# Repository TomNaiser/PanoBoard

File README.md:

# PanoBoard
Integrated Electronics Board for a Gigapixel Panorama Head (pan and tilt motion)
-Arduino nano based controller
-bluetooth communication with the windowsbased control notebook
-PID position control (modified RC-Servos)
-rotatory position encoders for precise position control 

The latest version PanoBoardV5 is a size-reduced version. With the shrunken electronics box the panorama rig fits into my photo backpack. 

## Arduino Nano R4 upgrade

The [PanoBoard V5 Nano R4 patch](PanoBoard5KiCad/Nano-R4-Patch.md) explains the resistor changes, GPIO current limits, encoder I²C pull-ups, power supply and firmware porting needed to replace the classic Nano with a Nano R4. The KiCad files remain the original V5 design; apply the documented rework before operating the R4.

Current software: [PanoDuinoControl firmware](https://github.com/TomNaiser/PanoDuinoControl), [Android app and system documentation](https://github.com/TomNaiser/PanoramaSoftware), and [PanoramaControl for Windows](https://github.com/TomNaiser/PanoramaControl).

Warning! The circuits in this project were designed as a hobbyist project and may contain unintentional mistakes.  I don't take any responsibility for damages caused by using the above circuit design. Please use the provided information at your own risk!

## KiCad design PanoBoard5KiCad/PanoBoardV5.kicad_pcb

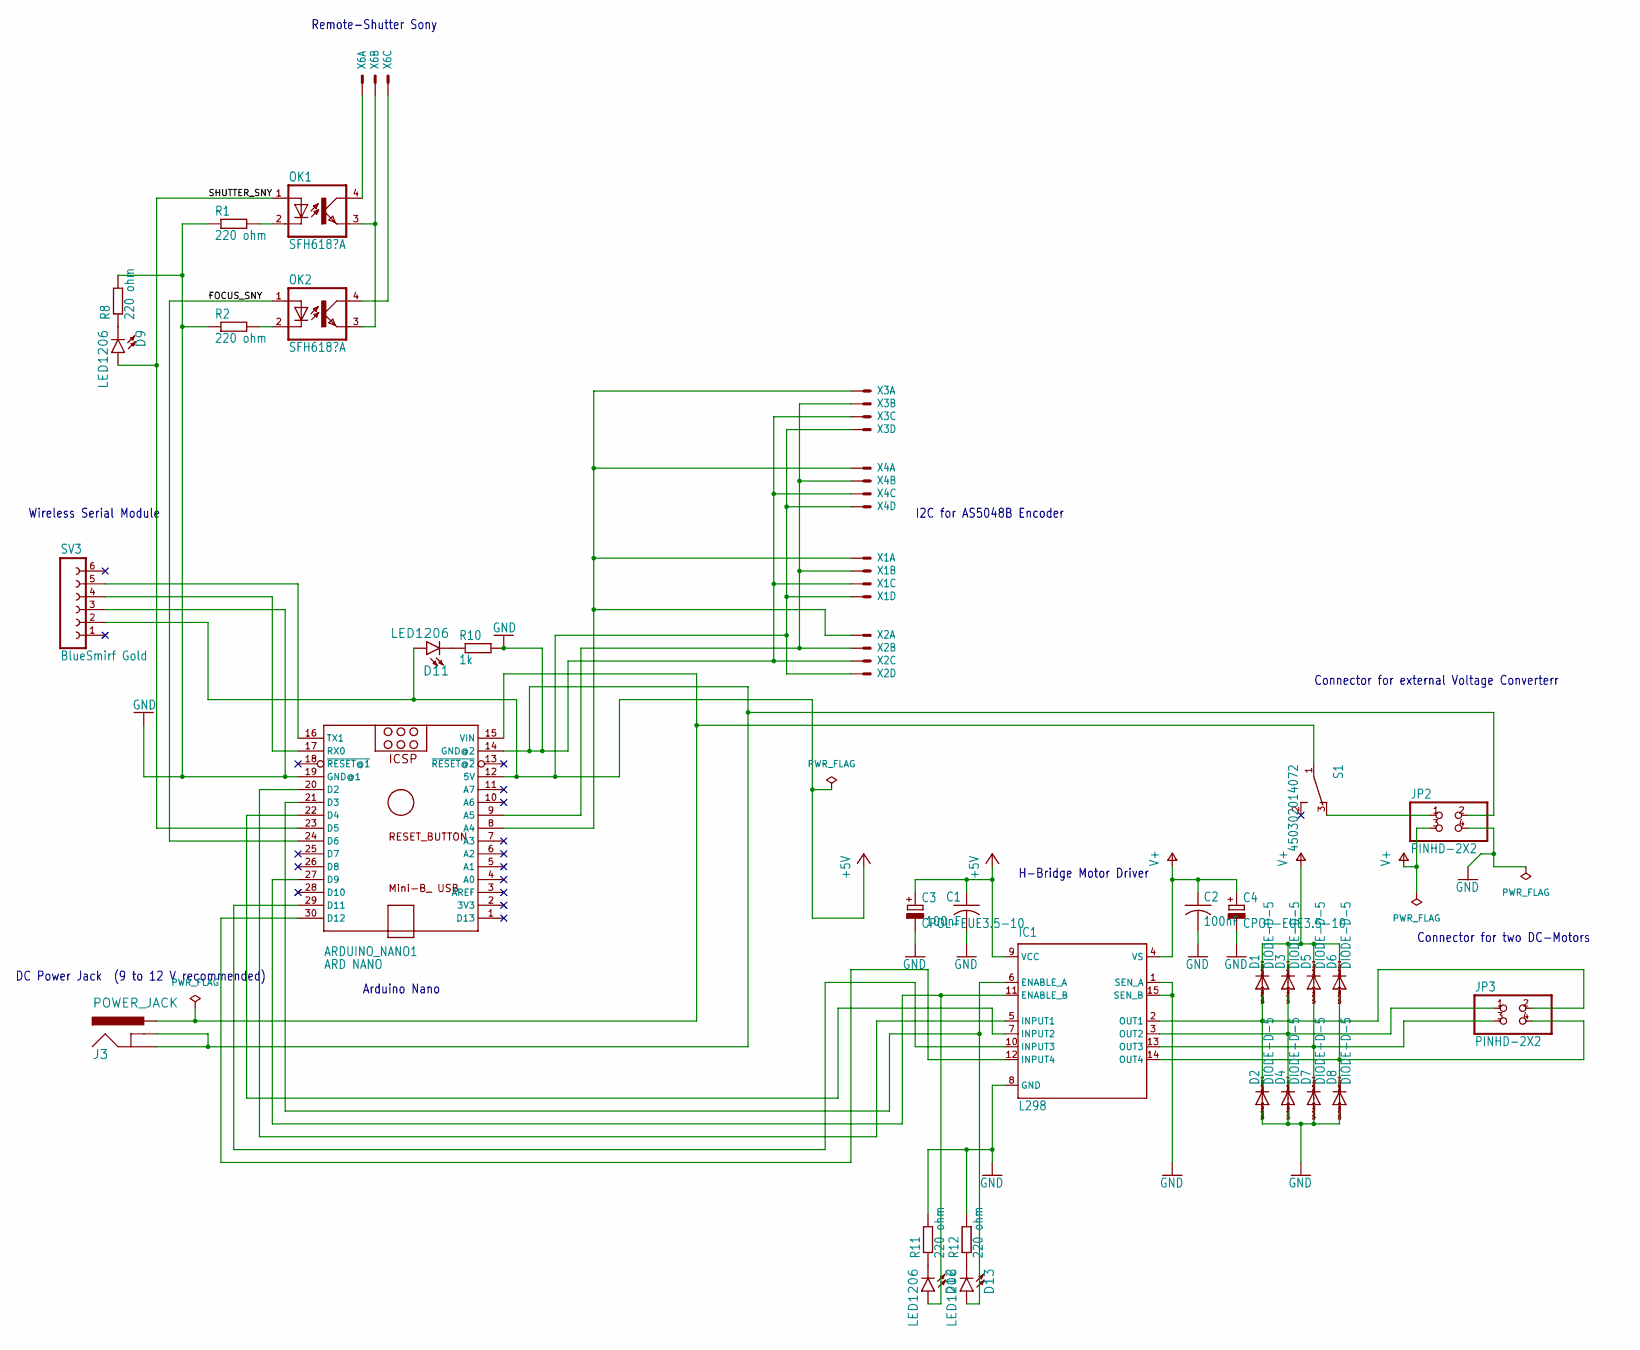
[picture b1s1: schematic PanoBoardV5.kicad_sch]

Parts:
ARDUINO_NANO1: ARD NANO; ARDUINO_NANO
C1, C2: 100nF; C050-024X044
C3, C4: CPOL-EUE3.5-10; E3,5-10
D1, D2, D3, D4, D5, D6, D7, D8: DIODE-D-5; D-5
D9, D11, D12, D13: LED1206; LED-1206
IC1: L298; MULTIWATT-15
J3: POWER_JACK; POWER_JACK_PTH
JP2, JP3: PINHD-2X2; 2X02
OK1, OK2: SFH618?A; DIP4
R1, R2, R8, R11, R12: 220 ohm; R1210
R10: 1k; R1210
S1: 450302014072
SV3: BlueSmirf Gold; FE06W
X1, X2: 53?-04047; 53047-04
X3, X4: 53?-04048; 53048-04
X6: 53?-03048; 53048-03

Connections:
+5V: ARDUINO_NANO1.12 (5V), C1.1, C3.+, D11.A, IC1.9 (VCC), SV3.2, X1.4 (S), X2.4 (S), X3.4 (S), X4.4 (S)
/FOCUS_SNY: ARDUINO_NANO1.24 (D6), OK2.1 (A)
/SHUTTER_SNY: ARDUINO_NANO1.23 (D5), D9.A, OK1.1 (A)
GND: ARDUINO_NANO1.14 (GND@2), ARDUINO_NANO1.19 (GND@1), C1.2, C2.2, C3.-, C4.-, D2.A, D4.A, D7.A, D8.A, IC1.1 (SEN_A), IC1.8 (GND), IC1.15 (SEN_B), J3.GND, J3.GNDBREAK, JP2.2, JP2.4, R1.1, R2.1, R8.2, R10.2, R11.2, R12.2, SV3.3, X1.3 (S), X2.3 (S), X3.3 (S), X4.3 (S)
unnamed: ARDUINO_NANO1.8 (A4), X1.1 (S), X2.1 (S), X3.1 (S), X4.1 (S)
unnamed: ARDUINO_NANO1.9 (A5), X1.2 (S), X2.2 (S), X3.2 (S), X4.2 (S)
unnamed: ARDUINO_NANO1.15 (VIN), J3.PWR, S1.1
unnamed: ARDUINO_NANO1.16 (TX1), SV3.5
unnamed: ARDUINO_NANO1.17 (RX0), SV3.4
unnamed: ARDUINO_NANO1.20 (D2), IC1.5 (INPUT1)
unnamed: ARDUINO_NANO1.21 (D3), D13.A, IC1.6 (ENABLE_A)
unnamed: ARDUINO_NANO1.22 (D4), IC1.7 (INPUT2)
unnamed: ARDUINO_NANO1.27 (D9), D12.A, IC1.11 (ENABLE_B)
unnamed: ARDUINO_NANO1.29 (D11), IC1.10 (INPUT3)
unnamed: ARDUINO_NANO1.30 (D12), IC1.12 (INPUT4)
unnamed: D1.A, D2.C, IC1.2 (OUT1), JP3.2
unnamed: D3.A, D4.C, IC1.3 (OUT2), JP3.1
unnamed: D5.A, D7.C, IC1.13 (OUT3), JP3.3
unnamed: D6.A, D8.C, IC1.14 (OUT4), JP3.4
unnamed: D9.C, R8.1
unnamed: D11.C, R10.1
unnamed: D12.C, R11.1
unnamed: D13.C, R12.1
unnamed: JP2.1, S1.3
unnamed: OK1.2 (C), R1.2
unnamed: OK1.3 (EMIT), OK2.3 (EMIT), X6.2 (S)
unnamed: OK1.4 (COL), X6.1 (S)
unnamed: OK2.2 (C), R2.2
unnamed: OK2.4 (COL), X6.3 (S)
V+: C2.1, C4.+, D1.C, D3.C, D5.C, D6.C, IC1.4 (VS), JP2.3

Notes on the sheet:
Connector for external Voltage Converterr
I2C for AS5048B Encoder
Connector for two DC-Motors
DC Power Jack (9 to 12 V recommended)
H-Bridge Motor Driver
Remote-Shutter Sony
Wireless Serial Module
Arduino Nano

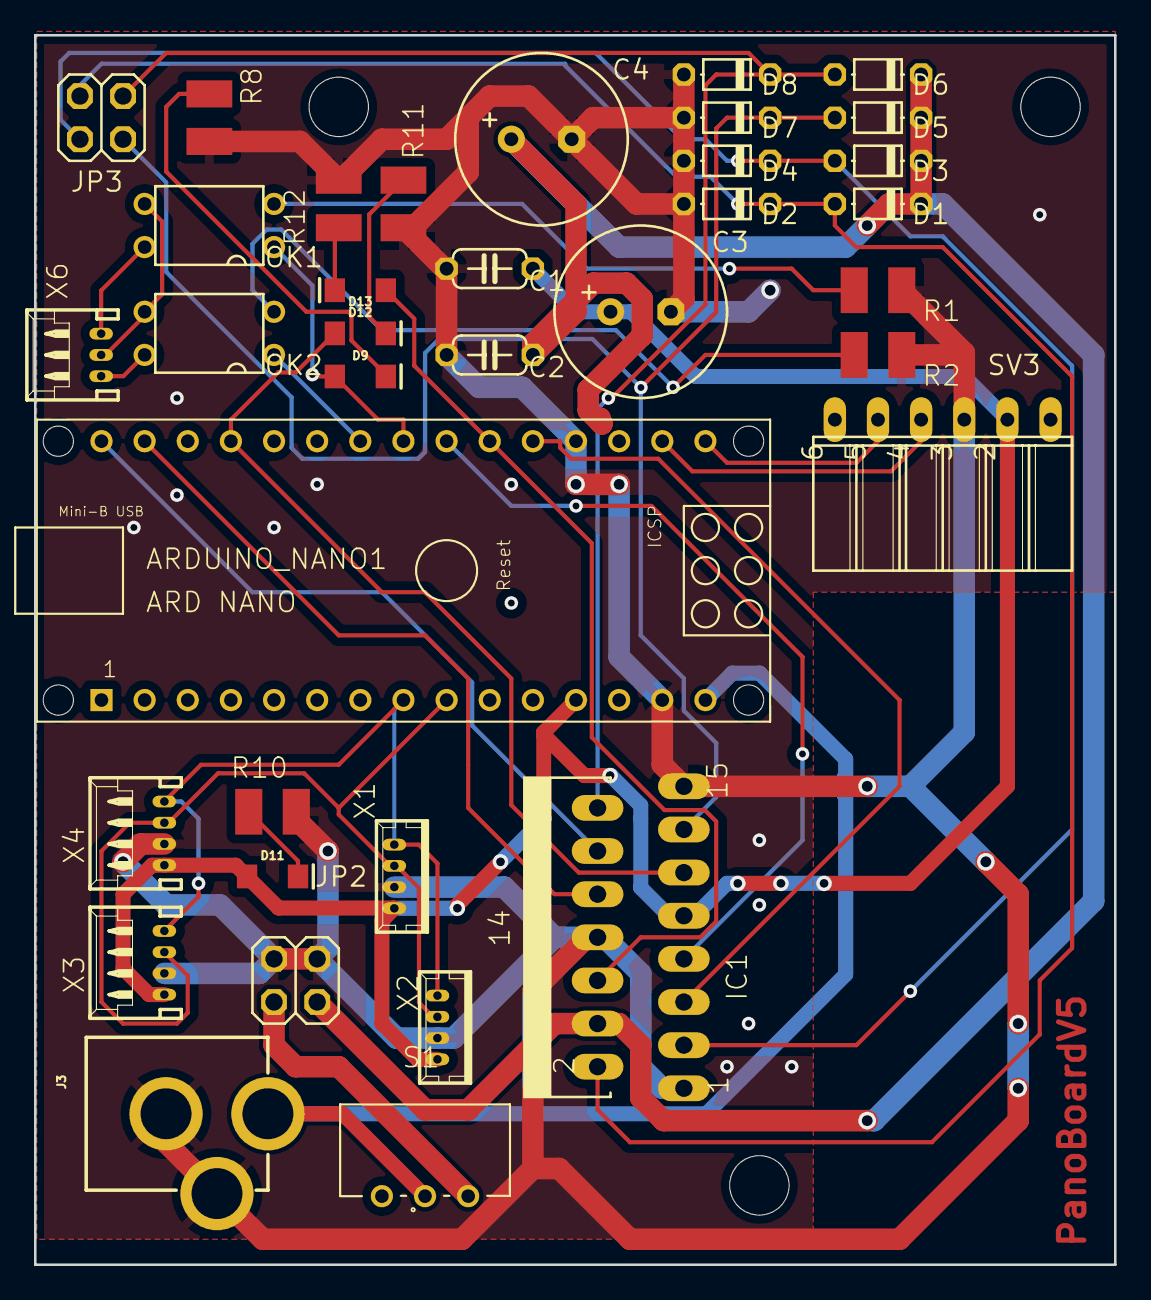
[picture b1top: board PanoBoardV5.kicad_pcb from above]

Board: 2 copper layers, 63.6 x 72.4 mm, 39 parts (0 on the bottom side), 30 nets.

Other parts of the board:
@HOLE0, @HOLE2, @HOLE3: (no value)

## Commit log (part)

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2019-05-11 Set theme jekyll-theme-cayman
2019-05-11 Parts List
2023-01-01 PanoBoardV5
    Simplified version of the board. Reduced footprint. Camera Triggering support only the Sony A7
2023-01-01 Photos of the board
